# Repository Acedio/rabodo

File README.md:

# rabodo (ラボード)

A leverless layout utilizing GP2040-CE. Planning to add a laser-cut
acryllic/wood case.

Runs GP2040-CE on the attached WaveShare RP2040-Zero.

## Assembly details

 - The PCB and case are designed to be held together with short (6mm) M4 screws
   and threaded heat-set inserts. The heat-set inserts are not actually melted
   into the acrylic, they were just the right form-factor for what I needed :)
 - I found 3mm acrylic was a good thickness for the top and bottom layers. The
   mid-layers on my final board were 3mm below the PCB and 4mm (2x2mm) above the
   PCB.
 - For the Kailh Choc V1 buttons, I've been experimenting with
   [these](https://www.printables.com/model/290182-arcade-button-caps-for-mx-and-kailh-low-profile-ke),
   but I'm finding it hard to keep them glued. I've not tried melting the PLA
   together yet, though, as I don't have a soldering tip I'm willing to
   sacrifice 😅
   [These](https://www.printables.com/model/176451-three-piece-flatbox-buttons-sturdier-prongs)
   seem like another promising option.

## Acknowledgements and thanks!

PCB is based on the [Flatbox](https://github.com/jfedor2/flatbox) design,
specifically the Rev5. Also takes a lot of case inspiration from the
[Dural](https://github.com/BatiKING/DURAL_DIY) project! Thank you to jfedor2 and
BatiKING for your awesome work on these.

Also a huge thanks to all the contributors on the
[GP2040-CE](https://github.com/OpenStickCommunity/GP2040-CE) project! Excellent
firmware and community :D Special thanks to
[TheTrain](https://github.com/TheTrainGoes) for help reviewing the PCB before
printing!

PCB and case design licensed under CC BY-SA 4.0.

PCB design uses the following:

 - keyswitches.pretty by daprice (CC BY-SA 4.0)
     * Modified to add silkscreen where caps will go.
 - RP2040-Zero STEP file downloaded from Waveshare wiki

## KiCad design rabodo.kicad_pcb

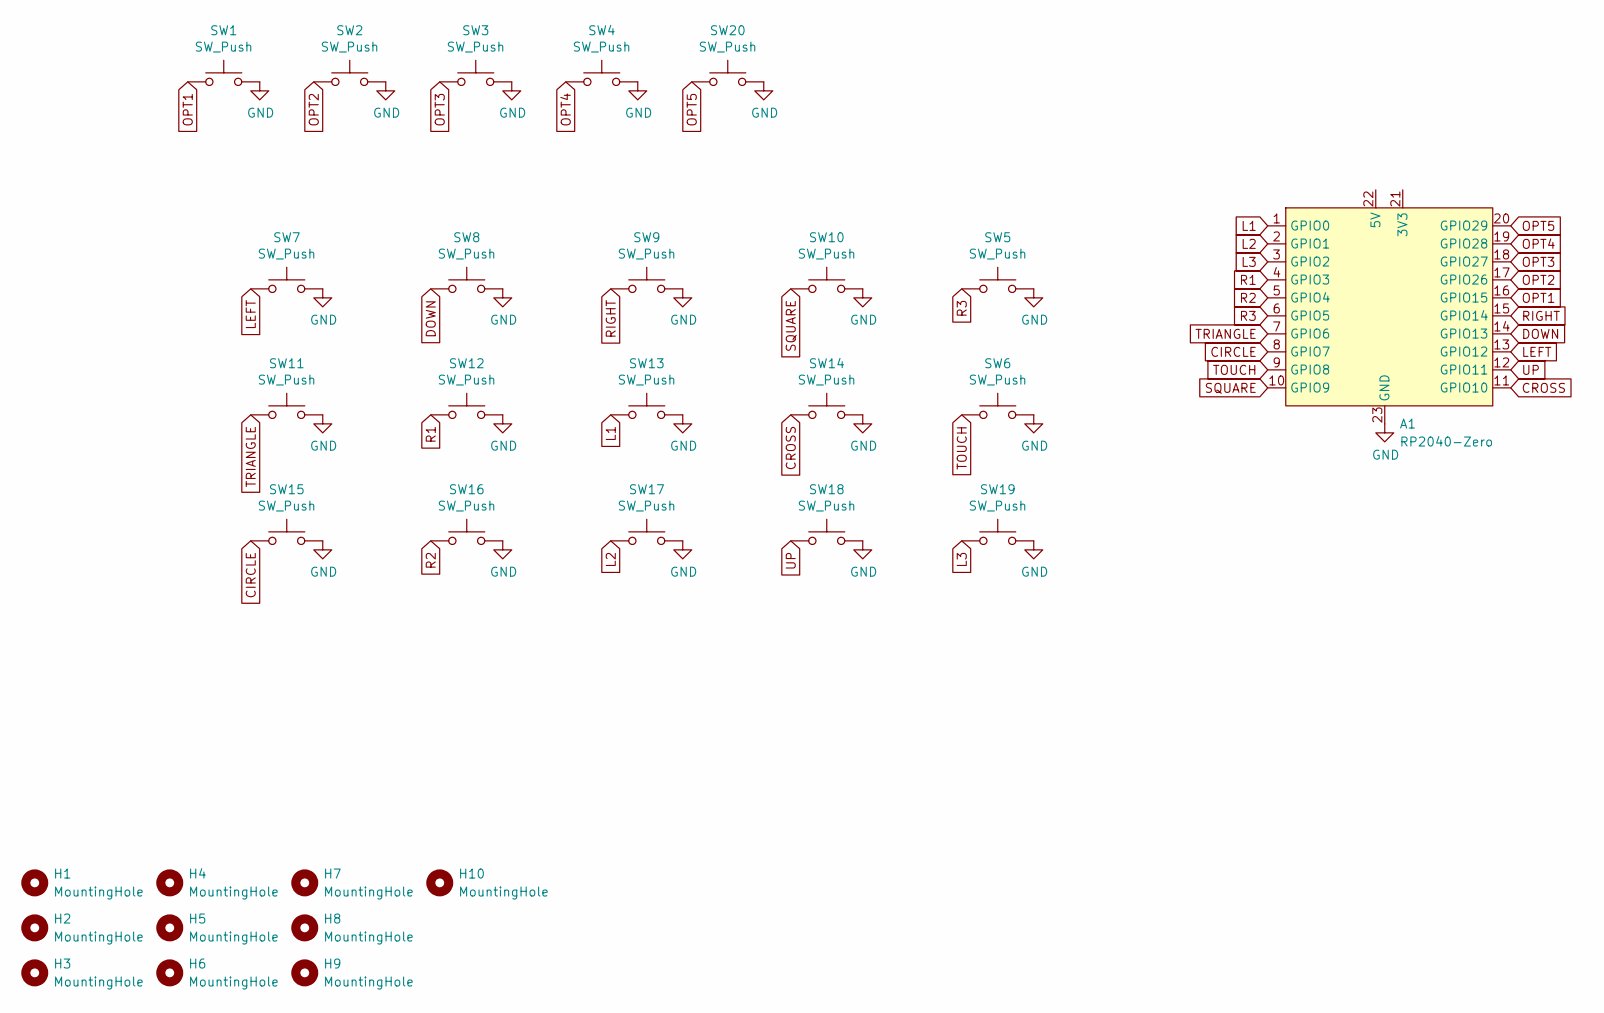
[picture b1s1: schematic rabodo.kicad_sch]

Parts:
A1: RP2040-Zero
H1, H2, H3, H4, H5, H6, H7, H8, H9, H10: MountingHole; MountingHole_6.4mm_M6
SW1, SW2, SW3, SW4, SW20: SW_Push; SW_PUSH_6mm_H5mm
SW5, SW6, SW7, SW8, SW9, SW10, SW11, SW12, SW13, SW14, SW15, SW16, SW17, SW18, SW19: SW_Push; Kailh_socket_PG1350_optional

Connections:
CIRCLE: A1.8 (GPIO7), SW15.1
CROSS: A1.11 (GPIO10), SW14.1
DOWN: A1.14 (GPIO13), SW8.1
GND: A1.23 (GND), SW1.2, SW2.2, SW3.2, SW4.2, SW5.2, SW6.2, SW7.2, SW8.2, SW9.2, SW10.2, SW11.2, SW12.2, SW13.2, SW14.2, SW15.2, SW16.2, SW17.2, SW18.2, SW19.2, SW20.2
L1: A1.1 (GPIO0), SW13.1
L2: A1.2 (GPIO1), SW17.1
L3: A1.3 (GPIO2), SW19.1
LEFT: A1.13 (GPIO12), SW7.1
OPT1: A1.16 (GPIO15), SW1.1
OPT2: A1.17 (GPIO26), SW2.1
OPT3: A1.18 (GPIO27), SW3.1
OPT4: A1.19 (GPIO28), SW4.1
OPT5: A1.20 (GPIO29), SW20.1
R1: A1.4 (GPIO3), SW12.1
R2: A1.5 (GPIO4), SW16.1
R3: A1.6 (GPIO5), SW5.1
RIGHT: A1.15 (GPIO14), SW9.1
SQUARE: A1.10 (GPIO9), SW10.1
TOUCH: A1.9 (GPIO8), SW6.1
TRIANGLE: A1.7 (GPIO6), SW11.1
UP: A1.12 (GPIO11), SW18.1

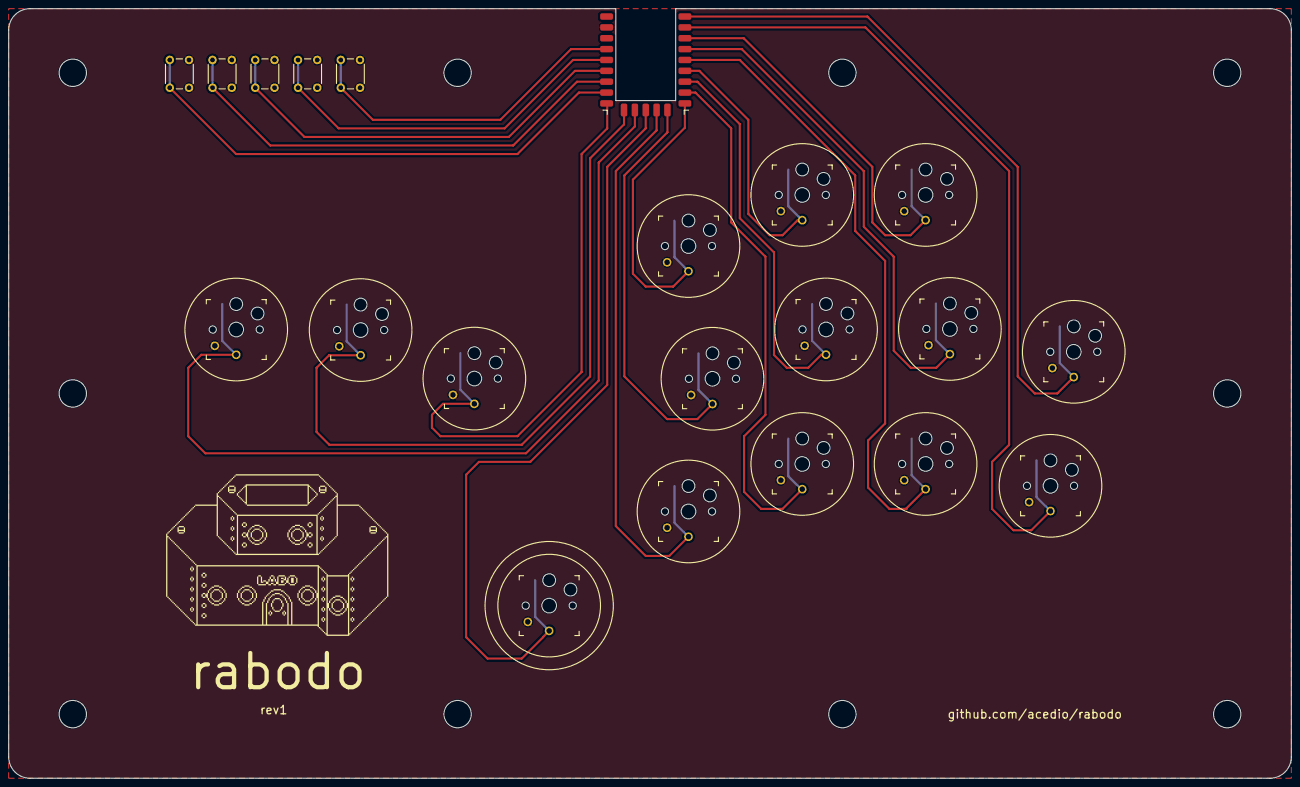
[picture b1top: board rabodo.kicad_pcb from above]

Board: 2 copper layers, 300.0 x 180.0 mm, 31 parts (0 on the bottom side), 21 nets.

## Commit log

2023-10-31 Initial commit. Not wired.
2023-11-01 Wiring, but unfilled?
2023-11-01 Fill.
2023-11-01 Cleaning up unused tracks.
2023-11-01 Renaming!
2023-11-01 Updating readme formatting.
2023-11-05 Expanding and rewiring board.
2023-11-05 Updating to use new Kailh footprint.
2023-11-05 Reverting to non-fancy traces and adding gerbers.
2023-11-05 Updating PCB image.
2023-11-05 Updating readme.
2023-11-05 Adding more thanks.
2023-11-06 Updating to fill the front of the PCB with a ground plane and widening the traces + spacing.
2023-11-07 Adding the button layer DXF.
2023-11-17 Adding top and bottom layers to case.
    Also fixing a spacing issue at the bottom of the mainboard.
2023-11-26 Adding the case files and a photo of the assembled board.
